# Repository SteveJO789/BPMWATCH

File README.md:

# BPMWATCH

BPMWATCH is a two-node wearable Radar MVP built with ESP32, B&T BU01/DW1000 ranging, GY-511 heading and motion sensing, MAX30102 heart-rate sensing, ESP-NOW Peer data, and a no-CS ZJY-IPS130-V2.0 ST7789 240x240 display.

Each node places itself at the center of a north-up radar screen and shows the other node as a distance-scaled dot. The direction is a movement-based visual estimate, not a true UWB angle measurement.

## Current Architecture

The product has two equal Radar Nodes:

| Product node | ESP32 STA MAC | Fixed DW1000 role |
|---|---|---|
| Node A | `0C:8A:D3:7C:E5:A4` | Anchor |
| Node B | `1C:75:C4:F4:E9:D4` | Tag |

Anchor and Tag are radio protocol roles only. There is no application-level Master or Slave.

The two links have separate responsibilities:

- **UWB:** calibrated distance ranging only.
- **ESP-NOW:** Peer BPM and accepted reciprocal-bearing estimates.

Production firmware will not create a Wi-Fi AP, webserver, or browser dashboard. The existing AP monitor remains only in the diagnostic `uwb_pair_test`.

See:

- [Architecture workflow](radar_2d_map_architecture.svg)
- [Architecture](docs/architecture.md)
- [Radar MVP design spec](docs/superpowers/specs/2026-06-21-radar-2d-map-mvp-design.md)
- [Test plan](docs/test-plan.md)

## Hardware Per Node

- ESP32-WROOM-32
- B&T BU01 DW1000 LDO UWB breakout
- ZJY-IPS130-V2.0 IPS TFT LCD 240x240 ST7789 display without a CS pin
- GY-511 / LSM303DLHC accelerometer and compass
- MAX30102 heart-rate sensor
- 602030 Li-Po battery
- TP4056 Type-C charger with protection
- TPS63802 3.3V buck-boost supply
- Power switch, decoupling capacitors, and enclosure

Both nodes use the same buses and pin map. Only the MAC address and fixed DW1000 role differ.

## Radar Behavior

- North-up display with the current node at `(120,120)`.
- UWB distance is filtered with an EMA and mapped to an automatic `5/10/20/40m` range.
- GY-511 acceleration and compass heading provide a visual movement-bearing heuristic.
- Decreasing distance places the Peer along the estimated movement bearing.
- Increasing distance places the Peer approximately 180 degrees behind that bearing.
- ESP-NOW mirrors an accepted bearing to the other display with a reciprocal 180-degree transform.
- If UWB is lost, the last Peer dot remains as an inactive outline.
- If ESP-NOW is stale, radar ranging continues and Peer BPM displays `--`.

## Repository Map

- `firmware/radar_node`: approved production target; implementation pending.
- `firmware/tests/uwb_pair_test`: working two-node UWB diagnostic with AP monitor.
- `firmware/tests`: focused hardware bring-up projects.
- `firmware/master` and `firmware/slave`: deprecated pre-pivot production scaffolds; scheduled for legacy relocation during firmware implementation.
- `firmware/sim/wokwi`: legacy three-node UI simulation; not current Radar MVP validation.
- `lib/DW1000`: vendored ESP32-compatible DW1000 library.
- `docs/legacy/three-node`: superseded triangle-map documents and diagrams.
- `test-logs`: current two-node bench evidence.

## Current Status

Completed:

- ESP32 identity and STA MAC capture.
- ZJY-IPS130-V2.0 display bring-up using dedicated `SPIClass`, manual reset, `SPI_MODE3`, and 8 MHz display transactions.
- GY-511 I2C discovery, initialization, and heading output.
- MAX30102 raw IR and BPM calculation bring-up.
- Real Node A to Node B DW1000 ranging.
- Antenna delay `16555`, five-sample application median filter, and recovery behavior.
- Two-node Radar architecture, glossary, workflow SVG, and design specification.

Next implementation milestone:

1. Create the shared `firmware/radar_node` PlatformIO project.
2. Integrate UWB range callbacks without the production AP monitor.
3. Add GY-511 movement-bearing estimation and axis mapping.
4. Add ESP-NOW Peer BPM and reciprocal bearing.
5. Render and bench-test the radar on both ST7789 displays.

## Diagnostic Build

On this Windows machine, PlatformIO is available through:

```powershell
& "$env:USERPROFILE\.platformio\penv\Scripts\platformio.exe" run -d firmware\tests\uwb_pair_test -e master -e tag
```

The diagnostic environments retain the literal names `master` and `tag` for compatibility with tested code. They map to Node A/Anchor and Node B/Tag.

## Electrical Safety

- Keep all ESP32, DW1000, ST7789, GY-511, and MAX30102 signal levels 3.3V-compatible.
- Confirm the exact BU01 breakout power-input label before applying power.
- Keep the no-CS ST7789 on dedicated HSPI; do not share the DW1000 default SPI bus.
- Initialize ZJY-IPS130-V2.0 with `tft.init(240, 240, SPI_MODE3)` and call `tft.setSPISpeed(8000000)` after init.
- Feed Li-Po voltage to an ESP32 ADC only through a safe resistor divider.
- Verify TPS63802 stability during ESP32 radio and UWB current bursts.

## Historical Architecture

The former one-Master/two-Slave triangle map is no longer the product direction. Its documentation is retained under [`docs/legacy/three-node`](docs/legacy/three-node/README.md).

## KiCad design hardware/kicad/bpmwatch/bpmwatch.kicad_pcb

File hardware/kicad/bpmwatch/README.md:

# BPMWATCH KiCad Schematic Status

The KiCad files in this folder predate the 2026-06-21 two-node Radar pivot. They describe an unequal Master/repeated-Slave concept and are not the current wiring source of truth.

Use [`docs/pin-map.md`](../../../docs/pin-map.md), [`docs/wiring-node-a.md`](../../../docs/wiring-node-a.md), and [`docs/wiring-node-b.md`](../../../docs/wiring-node-b.md) for current bench wiring.

## Required Schematic Revision

The next schematic revision must contain two equivalent Radar Nodes:

- ESP32-WROOM-32
- BU01/DW1000 on default SPI
- No-CS ST7789 on dedicated HSPI
- GY-511 and MAX30102 on shared I2C GPIO21/22
- Protected Li-Po charging and TPS63802 3.3V rail

Only the node identity and fixed DW1000 Anchor/Tag role differ.

## Existing Artifact Use

The existing schematic and exports remain historical module-level interconnect references. They are not production PCB signoff, and their Master/Slave labels must not be copied into new designs.

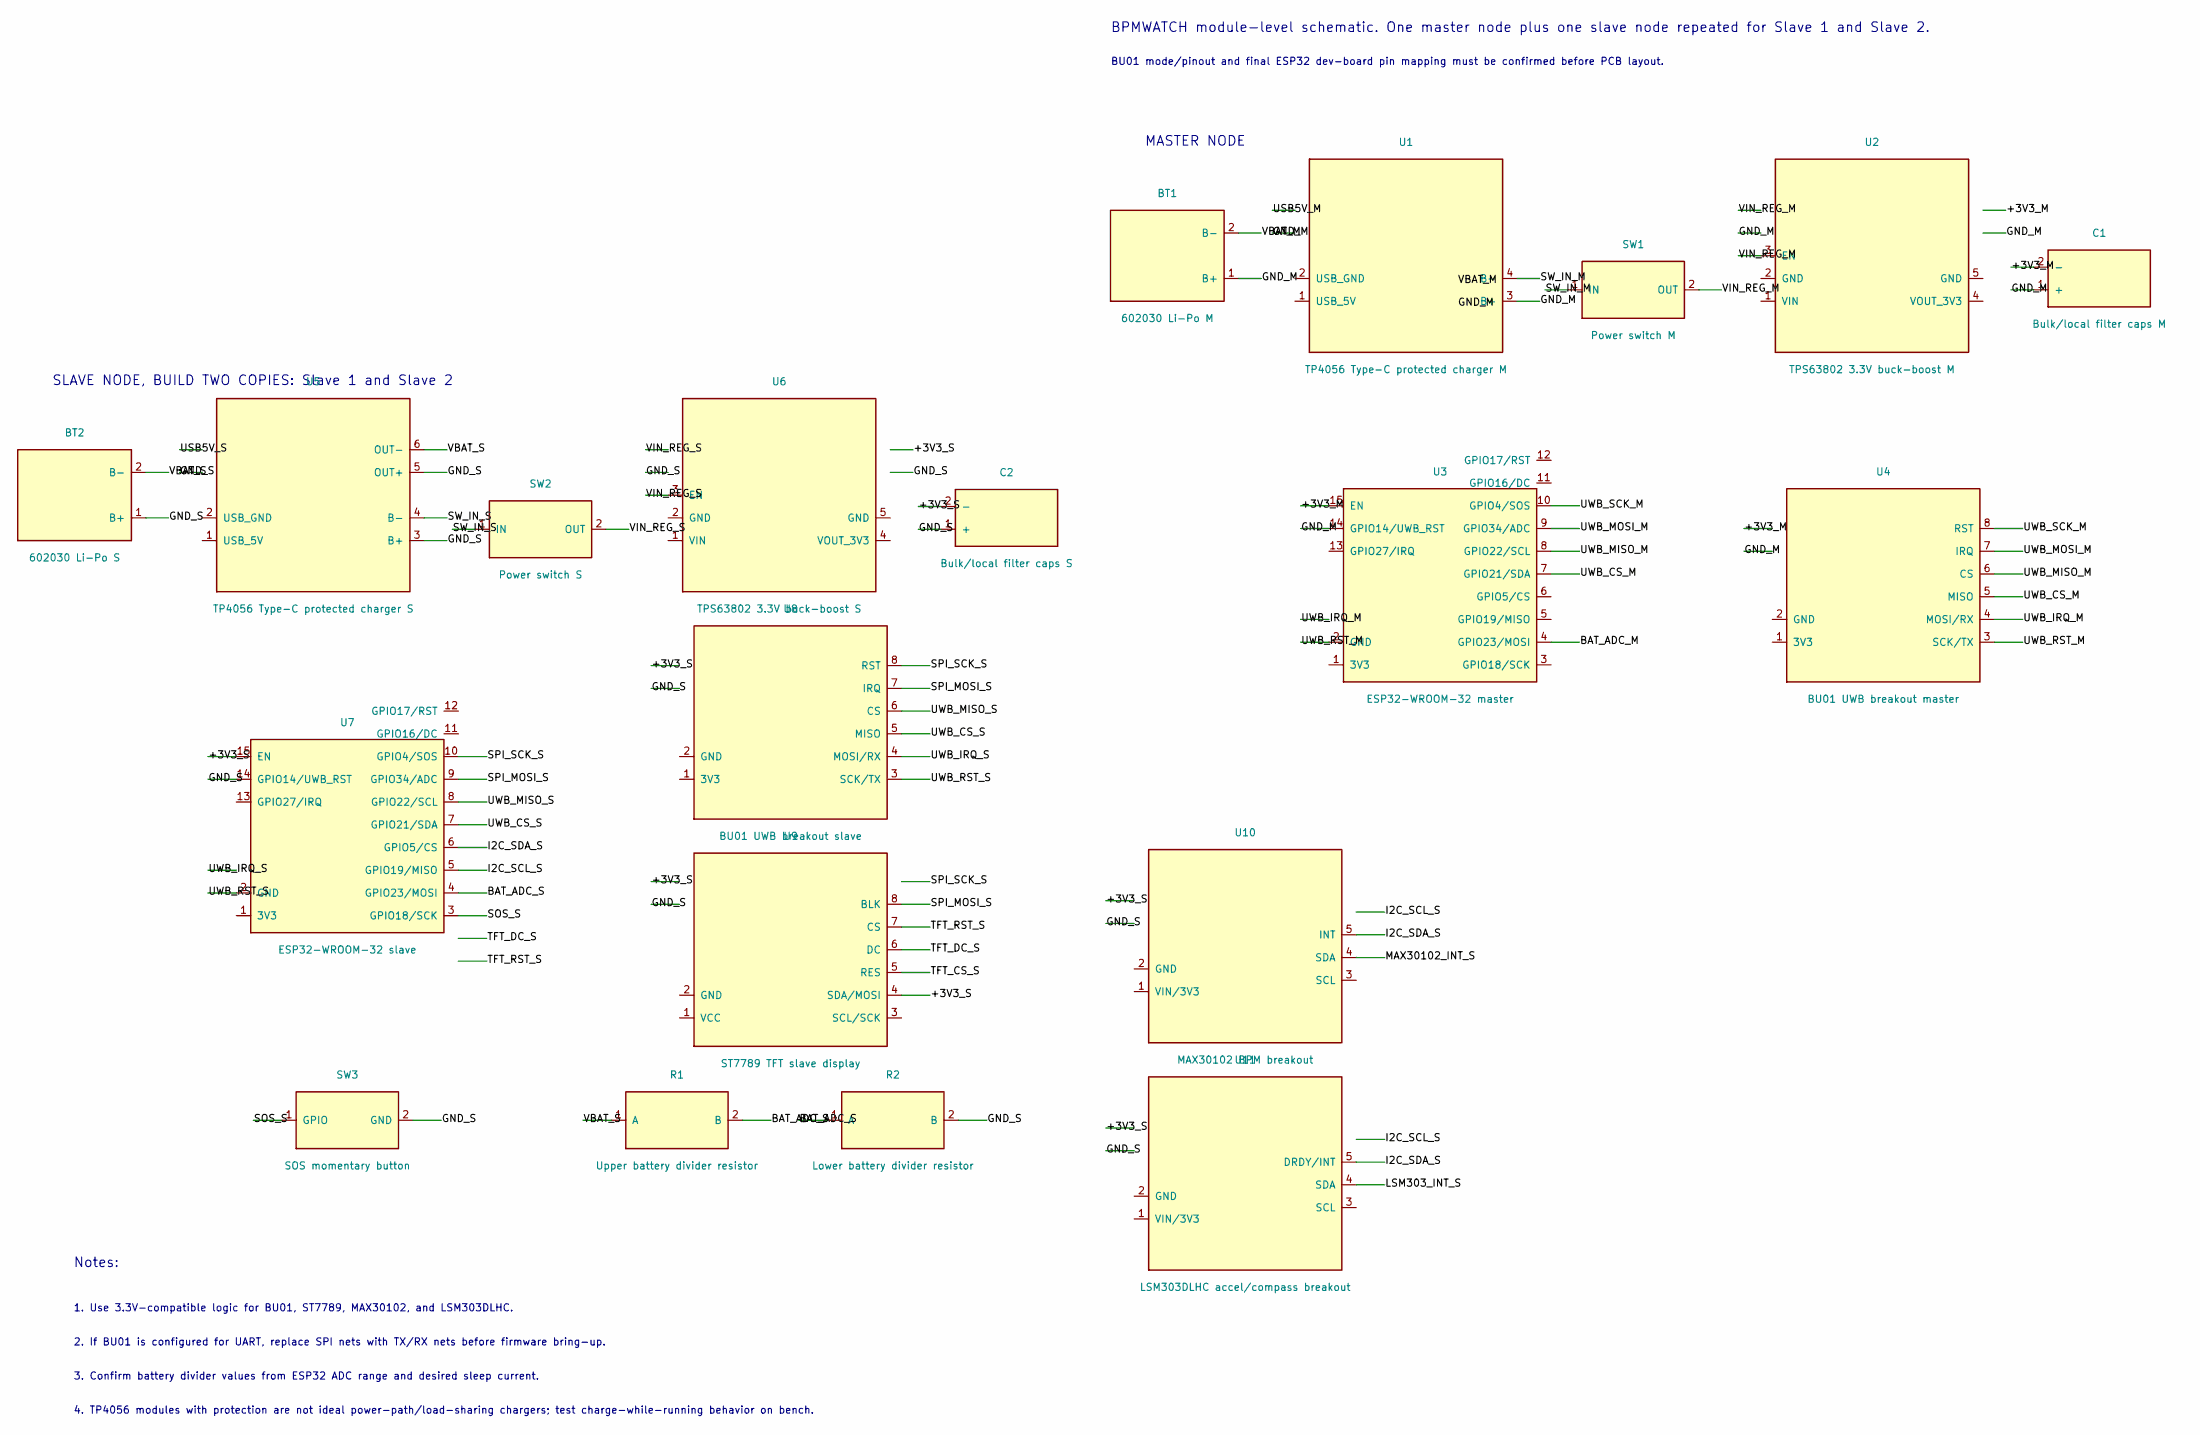
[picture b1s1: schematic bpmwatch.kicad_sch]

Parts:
BT1: 602030 Li-Po M; JST_PH_S2B-PH-K_1x02_P2.00mm_Horizontal
BT2: 602030 Li-Po S; JST_PH_S2B-PH-K_1x02_P2.00mm_Horizontal
C1: Bulk/local filter caps M; C_0805_2012Metric
C2: Bulk/local filter caps S; C_0805_2012Metric
R1: Upper battery divider resistor; R_0805_2012Metric
R2: Lower battery divider resistor; R_0805_2012Metric
SW1: Power switch M; SW_Slide_SPDT_Straight_CK_OS102011MS2Q
SW2: Power switch S; SW_Slide_SPDT_Straight_CK_OS102011MS2Q
SW3: SOS momentary button; SW_PUSH_6mm_H4.3mm
U1: TP4056 Type-C protected charger M; PinHeader_1x06_P2.54mm_Vertical
U2: TPS63802 3.3V buck-boost M; PinHeader_1x05_P2.54mm_Vertical
U3: ESP32-WROOM-32 master; ESP32-WROOM-32
U4: BU01 UWB breakout master; PinHeader_1x08_P2.54mm_Vertical
U5: TP4056 Type-C protected charger S; PinHeader_1x06_P2.54mm_Vertical
U6: TPS63802 3.3V buck-boost S; PinHeader_1x05_P2.54mm_Vertical
U7: ESP32-WROOM-32 slave; ESP32-WROOM-32
U8: BU01 UWB breakout slave; PinHeader_1x08_P2.54mm_Vertical
U9: ST7789 TFT slave display; PinHeader_1x08_P2.54mm_Vertical
U10: MAX30102 BPM breakout; PinHeader_1x05_P2.54mm_Vertical
U11: LSM303DLHC accel/compass breakout; PinHeader_1x05_P2.54mm_Vertical

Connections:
+3V3_M: C1.2 (-), U3.15 (EN)
+3V3_S: C2.2 (-), U7.15 (EN), U9.4 (SDA/MOSI)
BAT_ADC_M: U3.4 (GPIO23/MOSI)
BAT_ADC_S: R1.2 (B), R2.1 (A), U7.4 (GPIO23/MOSI)
GND_M: BT1.1 (B+), C1.1 (+), U1.3 (B+), U3.14 (GPIO14/UWB_RST)
GND_S: BT2.1 (B+), C2.1 (+), R2.2 (B), SW3.2 (GND), U5.3 (B+), U5.5 (OUT+), U7.14 (GPIO14/UWB_RST)
I2C_SCL_S: U7.5 (GPIO19/MISO)
I2C_SDA_S: U7.6 (GPIO5/CS), U10.5 (INT), U11.5 (DRDY/INT)
LSM303_INT_S: U11.4 (SDA)
MAX30102_INT_S: U10.4 (SDA)
SOS_S: SW3.1 (GPIO), U7.3 (GPIO18/SCK)
SPI_MOSI_S: U7.9 (GPIO34/ADC), U8.7 (IRQ), U9.8 (BLK)
SPI_SCK_S: U7.10 (GPIO4/SOS), U8.8 (RST)
SW_IN_M: SW1.1 (IN), U1.4 (B-)
SW_IN_S: SW2.1 (IN), U5.4 (B-)
TFT_CS_S: U9.5 (RES)
TFT_DC_S: U9.6 (DC)
TFT_RST_S: U9.7 (CS)
UWB_CS_M: U3.7 (GPIO21/SDA), U4.5 (MISO)
UWB_CS_S: U7.7 (GPIO21/SDA), U8.5 (MISO)
UWB_IRQ_M: U4.4 (MOSI/RX)
UWB_IRQ_S: U8.4 (MOSI/RX)
UWB_MISO_M: U3.8 (GPIO22/SCL), U4.6 (CS)
UWB_MISO_S: U7.8 (GPIO22/SCL), U8.6 (CS)
UWB_MOSI_M: U3.9 (GPIO34/ADC), U4.7 (IRQ)
UWB_RST_M: U3.2 (GND), U4.3 (SCK/TX)
UWB_RST_S: U7.2 (GND), U8.3 (SCK/TX)
UWB_SCK_M: U3.10 (GPIO4/SOS), U4.8 (RST)
VBAT_M: BT1.2 (B-)
VBAT_S: BT2.2 (B-), R1.1 (A), U5.6 (OUT-)
VIN_REG_M: SW1.2 (OUT), U2.3 (EN)
VIN_REG_S: SW2.2 (OUT), U6.3 (EN)

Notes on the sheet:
MASTER NODE
BPMWATCH module-level schematic. One master node plus one slave node repeated for Slave 1 and Slave 2.
1. Use 3.3V-compatible logic for BU01, ST7789, MAX30102, and LSM303DLHC.
BU01 mode/pinout and final ESP32 dev-board pin mapping must be confirmed before PCB layout.
Notes:
SLAVE NODE, BUILD TWO COPIES: Slave 1 and Slave 2
2. If BU01 is configured for UART, replace SPI nets with TX/RX nets before firmware bring-up.
4. TP4056 modules with protection are not ideal power-path/load-sharing chargers; test charge-while-running behavior on bench.
3. Confirm battery divider values from ESP32 ADC range and desired sleep current.

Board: 2 copper layers, 20 parts (0 on the bottom side), 22 nets, no tracks yet.

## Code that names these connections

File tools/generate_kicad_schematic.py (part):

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        (
            Pin("1", "3V3", "left", -14, "power_in"),
            Pin("2", "GND", "left", -10, "power_in"),
            Pin("3", "GPIO18/SCK", "right", -14),
            Pin("4", "GPIO23/MOSI", "right", -10),
            Pin("5", "GPIO19/MISO", "right", -6),
            Pin("6", "GPIO5/CS", "right", -2),
            Pin("7", "GPIO21/SDA", "right", 2, "bidirectional"),
            Pin("8", "GPIO22/SCL", "right", 6),
            Pin("9", "GPIO34/ADC", "right", 10, "input"),
            Pin("10", "GPIO4/SOS", "right", 14, "input"),
            Pin("11", "GPIO16/DC", "right", 18),
            Pin("12", "GPIO17/RST", "right", 22),
            Pin("13", "GPIO27/IRQ", "left", 6, "input"),
            Pin("14", "GPIO14/UWB_RST", "left", 10),
            Pin("15", "EN", "left", 14, "input"),
        ),
        datasheet="https://www.espressif.com/sites/default/files/documentation/esp32-wroom-32_datasheet_en.pdf",
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
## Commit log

2026-06-06 Initial BPMWATCH relative 2D map project structure
2026-06-18 Update BPMWATCH hardware bring-up
2026-06-18 Add Arduino IDE UWB pair test guides
2026-06-19 feat: calculate BPM from MAX30102 readings
2026-06-19 feat: add UWB pair ranging monitor
2026-06-21 Improve UWB ranging recovery and filtering
2026-06-21 docs: design two-node radar MVP
2026-06-21 docs: migrate project to two-node radar architecture
2026-06-21 docs: design GY-511 Bluetooth monitor
2026-06-21 docs: design integrated node diagnostics
2026-06-21 integrated components
2026-06-24 analyze
2026-06-24 Improve integrated UWB diagnostics and recovery
2026-06-24 Improve integrated UWB diagnostics and MAX sampling
2026-06-24 Fix RF_TXCTRL verification and MAX diagnostics
2026-06-27 radar map added
2026-06-27 feat: improve radar espnow telemetry
2026-06-27 Fix MAX30102 wrist BPM validation
